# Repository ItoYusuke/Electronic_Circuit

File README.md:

Electronic_Circuit
==================

###Rubbish Devices Warehouse
##我楽多 デバイス 倉庫

Temporary list
 * I-Robot                : Motor driver and Sensor for robot.
 * LED_Blink              : Meaning as it is
 * LogicIC_CPU            : 74HCxx 4bit CPU
 * Optical_Communication  : LED or Laser light Optical communication
 * Voice_Synthesis-USB    : Voice synthesis LSI to PIC18F2550?
 * Libraries              : make devices for Eagle Libries

運用テストとして，過去の作品とかも含んでます．  
「体裁が保てていない」「処女作」「思いつき」の電子回路が多いです．  
そのうち突かれるか正式運用すると綺麗にします．  

--Implementation TEST--  
 * Eagle CAD + GitHub

A past work etc. are contained.  
"The appearance cannot be kept up. " "First work" "Straight Idea" etc...  
There are such a lot of electric circuits.   
Both are dirty.  
…It corrects it sooner or later.  

and... 

Please pay attention.   
Fool that I am!

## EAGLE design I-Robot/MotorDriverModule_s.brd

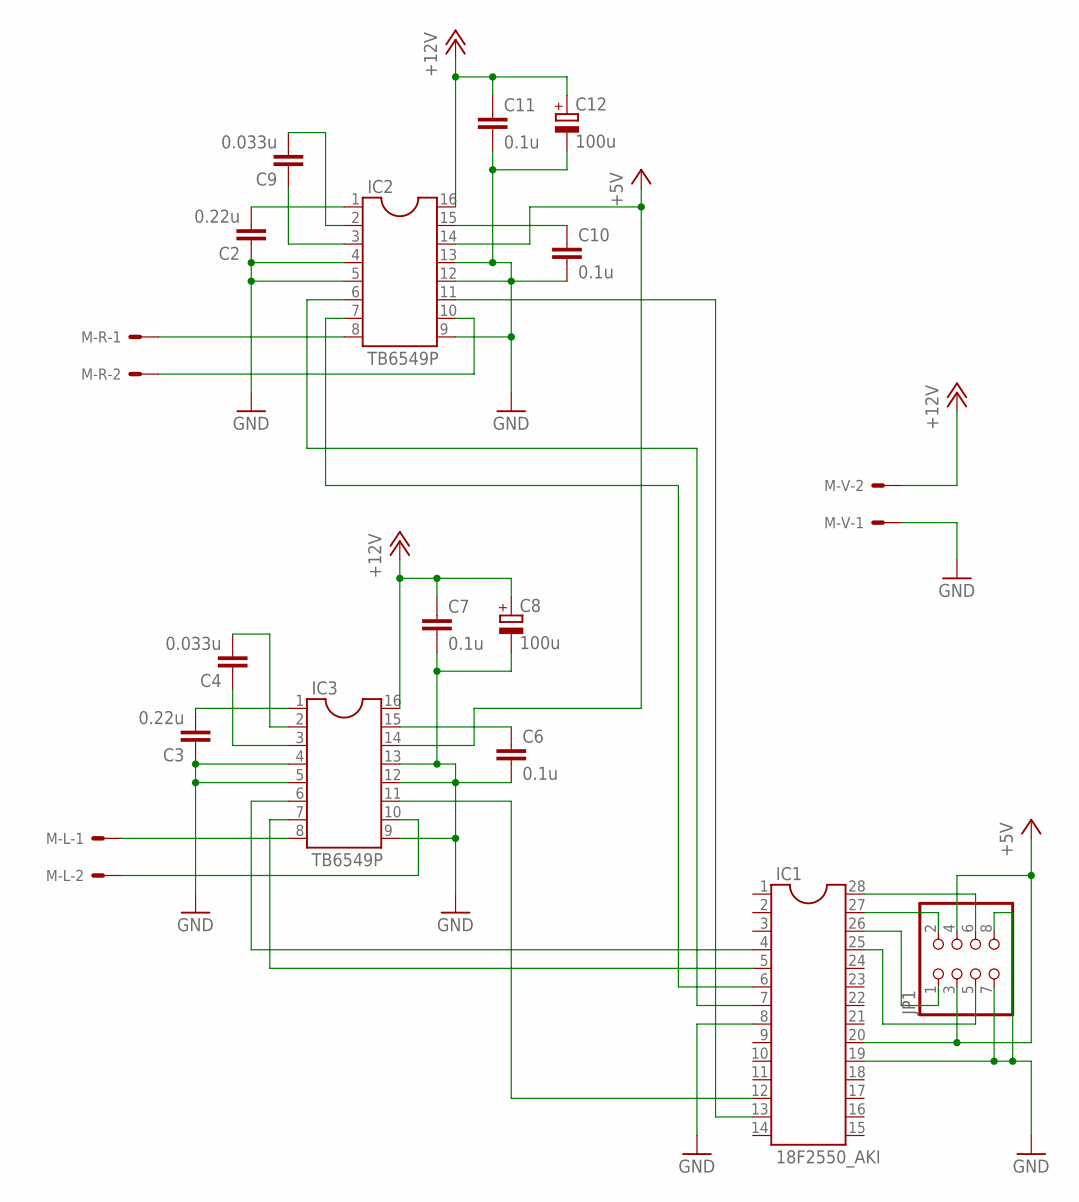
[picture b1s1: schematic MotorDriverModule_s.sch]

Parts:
C2, C3: 0.22u; C2012
C4, C9: 0.033u; C2012
C6, C7, C10, C11: 0.1u; C2012
C8, C12: 100u; D/7343-31W
IC1: 18F2550_AKI
IC2, IC3: TB6549P
JP1: PINHD-2X4; 2X04
M-L: KK-156-2
M-R: KK-156-2
M-V: KK-156-2

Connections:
+5V: IC1.20, IC2.14, IC3.14, JP1.3, JP1.4
+12V: C7.1, C8.+, C11.1, C12.+, IC2.16, IC3.16, M-V.2
GND: C2.1, C3.1, C6.2, C7.2, C8.-, C10.2, C11.2, C12.-, IC1.8, IC1.19, IC2.4, IC2.5, IC2.9, IC2.12, IC2.13, IC3.4, IC3.5, IC3.9, IC3.12, IC3.13, JP1.7, JP1.8, M-V.1
unnamed: IC1.12, IC3.11
unnamed: IC1.4, IC3.6
unnamed: IC1.5, IC3.7
unnamed: IC3.8, M-L.1
unnamed: IC3.10, M-L.2
unnamed: C3.2, IC3.1
unnamed: C4.2, IC3.2
unnamed: C4.1, IC3.3
unnamed: C6.1, IC3.15
unnamed: IC1.28, JP1.6
unnamed: IC1.13, IC2.11
unnamed: IC1.7, IC2.6
unnamed: IC1.6, IC2.7
unnamed: IC2.8, M-R.1
unnamed: IC1.27, JP1.2
unnamed: IC1.26, JP1.1
unnamed: IC1.25, JP1.5
unnamed: IC2.10, M-R.2
unnamed: C2.2, IC2.1
unnamed: C9.2, IC2.2
unnamed: C9.1, IC2.3
unnamed: C10.1, IC2.15

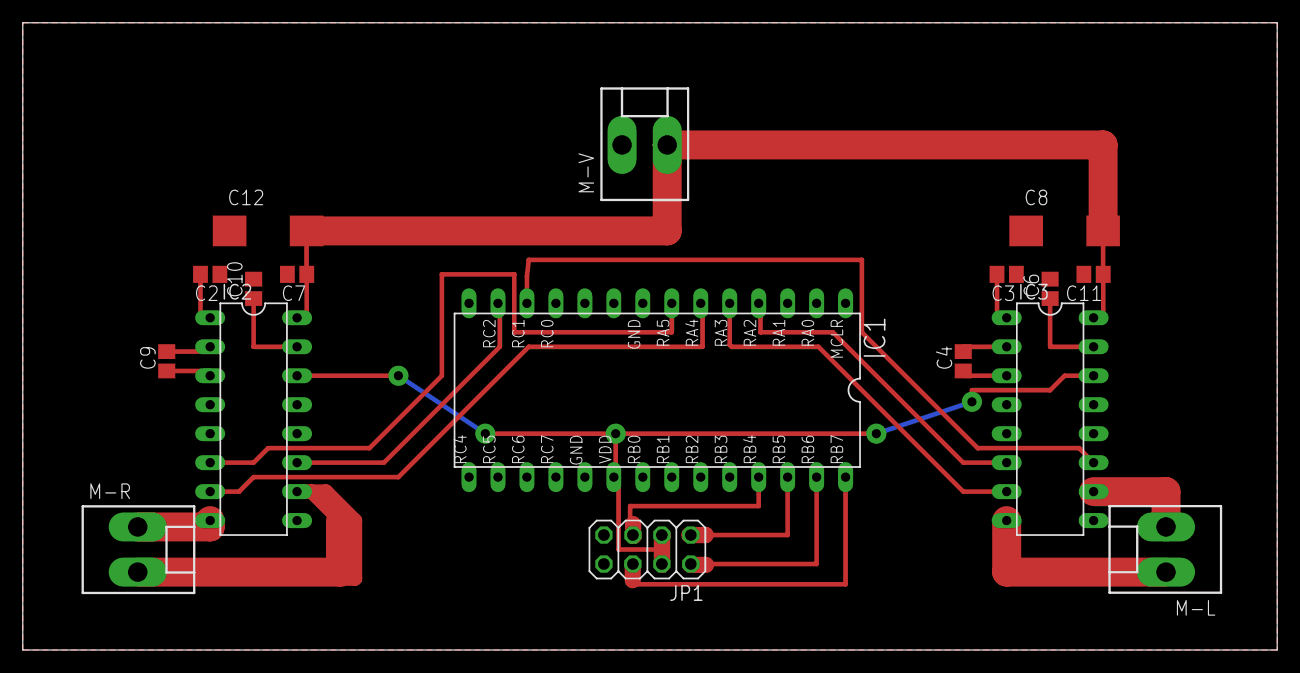
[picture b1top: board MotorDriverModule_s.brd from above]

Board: 2 copper layers, 110.0 x 55.0 mm, 17 parts (0 on the bottom side), 25 nets.

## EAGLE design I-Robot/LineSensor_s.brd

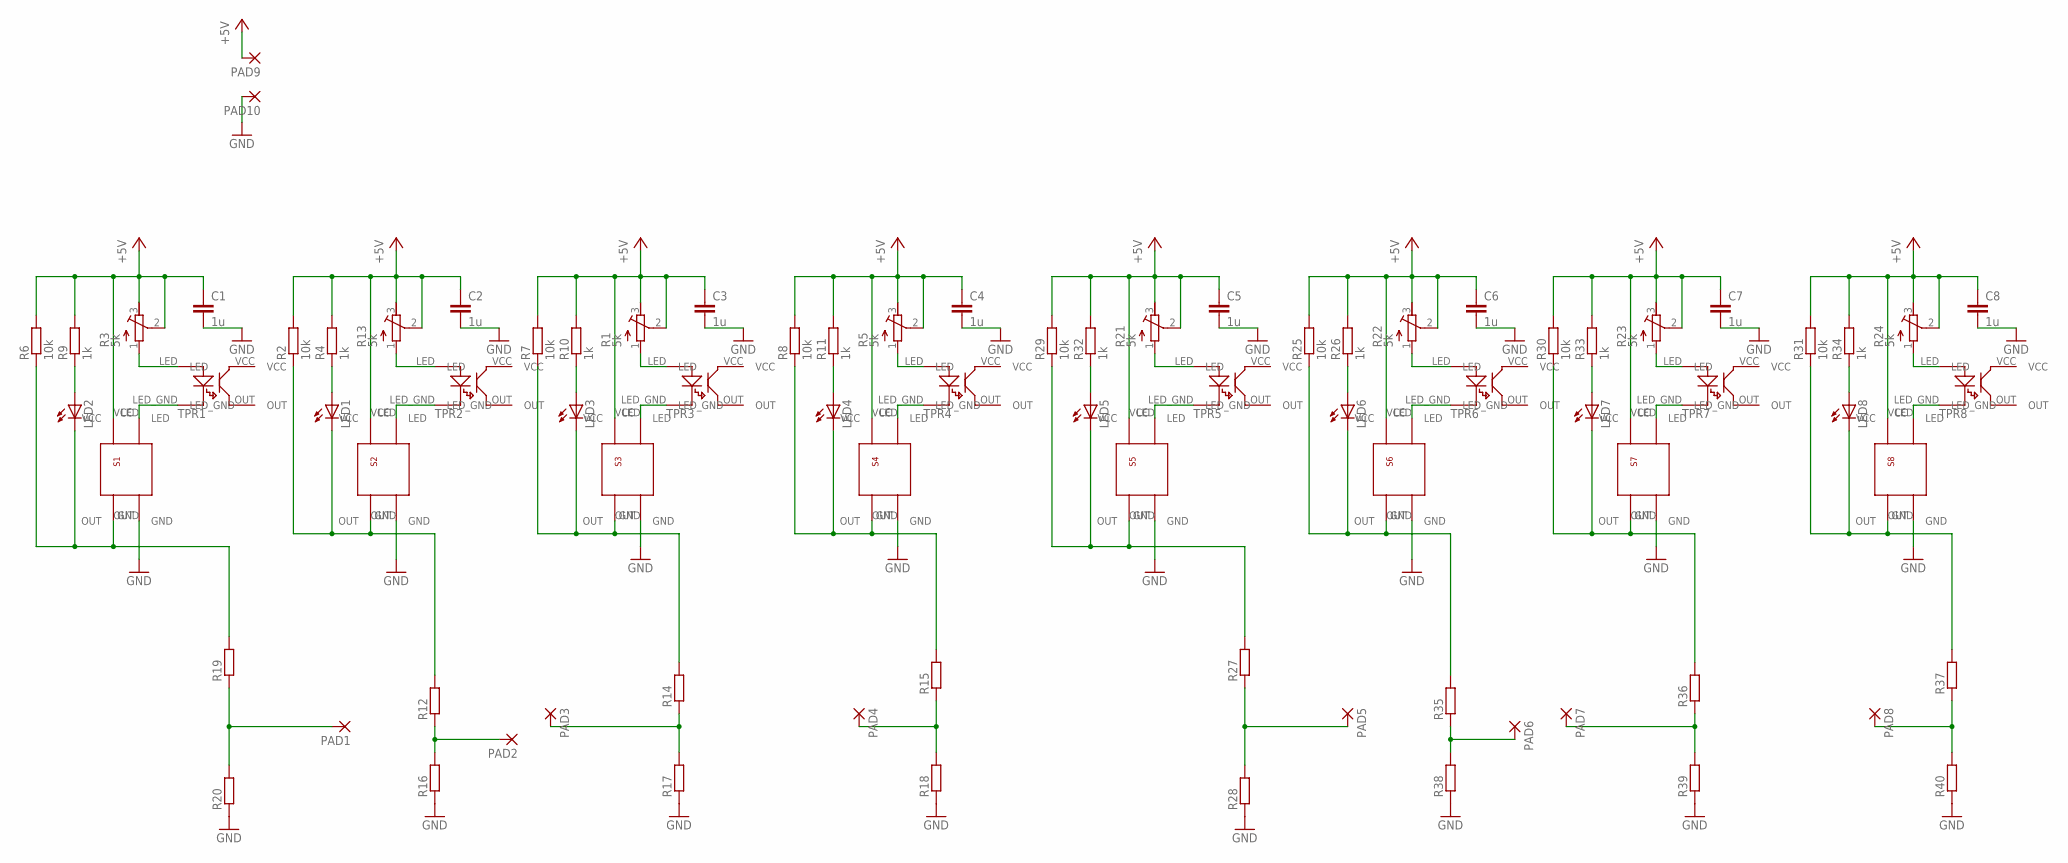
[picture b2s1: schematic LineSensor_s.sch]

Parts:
C1, C2, C3, C4, C5, C6, C7, C8: 1u; C1005
LED1, LED2, LED3, LED4, LED5, LED6, LED7, LED8: LEDSMT1206; 1206
PAD1, PAD2, PAD3, PAD4, PAD5, PAD6, PAD7, PAD8, PAD9, PAD10: SMD5; SMD2,54-5,08
R1, R3, R5, R13, R21, R22, R23, R24: 5k; RTRIM3374
R2, R6, R7, R8, R25, R29, R30, R31: 10k; R2012
R4, R9, R10, R11, R26, R32, R33, R34: 1k; R2012
R12, R14, R15, R16, R17, R18, R19, R20, R27, R28, R35, R36, R37, R38, R39, R40: R-EU_R2012; R2012
S1, S2, S3, S4, S5, S6, S7, S8: S-IC
TPR1, TPR2, TPR3, TPR4, TPR5, TPR6, TPR7, TPR8: TPR

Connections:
+5V: C1.1, C2.1, C3.1, C4.1, C5.1, C6.1, C7.1, C8.1, PAD9.1, R1.2 (S), R1.3 (A), R2.2, R3.2 (S), R3.3 (A), R4.2, R5.2 (S), R5.3 (A), R6.2, R7.2, R8.2, R9.2, R10.2, R11.2, R13.2 (S), R13.3 (A), R21.2 (S), R21.3 (A), R22.2 (S), R22.3 (A), R23.2 (S), R23.3 (A), R24.2 (S), R24.3 (A), R25.2, R26.2, R29.2, R30.2, R31.2, R32.2, R33.2, R34.2, S1.VCC, S2.VCC, S3.VCC, S4.VCC, S5.VCC, S6.VCC, S7.VCC, S8.VCC
GND: C1.2, C2.2, C3.2, C4.2, C5.2, C6.2, C7.2, C8.2, PAD10.1, R16.1, R17.1, R18.1, R20.1, R28.1, R38.1, R39.1, R40.1, S1.GND, S2.GND, S3.GND, S4.GND, S5.GND, S6.GND, S7.GND, S8.GND
unnamed: S2.LED, TPR2.LED_GND
unnamed: R13.1 (E), TPR2.LED
unnamed: S1.LED, TPR1.LED_GND
unnamed: R3.1 (E), TPR1.LED
unnamed: LED2.C, R6.1, R19.2, S1.OUT
unnamed: LED2.A, R9.1
unnamed: LED1.C, R2.1, R12.2, S2.OUT
unnamed: LED1.A, R4.1
unnamed: S3.LED, TPR3.LED_GND
unnamed: R1.1 (E), TPR3.LED
unnamed: LED3.C, R7.1, R14.2, S3.OUT
unnamed: LED3.A, R10.1
unnamed: S4.LED, TPR4.LED_GND
unnamed: R5.1 (E), TPR4.LED
unnamed: LED4.C, R8.1, R15.2, S4.OUT
unnamed: LED4.A, R11.1
unnamed: PAD2.1, R12.1, R16.2
unnamed: PAD3.1, R14.1, R17.2
unnamed: PAD4.1, R15.1, R18.2
unnamed: S5.LED, TPR5.LED_GND
unnamed: R21.1 (E), TPR5.LED
unnamed: LED5.C, R27.2, R29.1, S5.OUT
unnamed: LED5.A, R32.1
unnamed: S6.LED, TPR6.LED_GND
unnamed: R22.1 (E), TPR6.LED
unnamed: LED6.C, R25.1, R35.2, S6.OUT
unnamed: LED6.A, R26.1
unnamed: S7.LED, TPR7.LED_GND
unnamed: R23.1 (E), TPR7.LED
unnamed: LED7.C, R30.1, R36.2, S7.OUT
unnamed: LED7.A, R33.1
unnamed: S8.LED, TPR8.LED_GND
unnamed: R24.1 (E), TPR8.LED
unnamed: LED8.C, R31.1, R37.2, S8.OUT
unnamed: LED8.A, R34.1
unnamed: PAD5.1, R27.1, R28.2
unnamed: PAD6.1, R35.1, R38.2
unnamed: PAD7.1, R36.1, R39.2
unnamed: PAD8.1, R37.1, R40.2
unnamed: PAD1.1, R19.1, R20.2
VCC: TPR1.VCC, TPR2.VCC, TPR3.VCC, TPR4.VCC, TPR5.VCC, TPR6.VCC, TPR7.VCC, TPR8.VCC

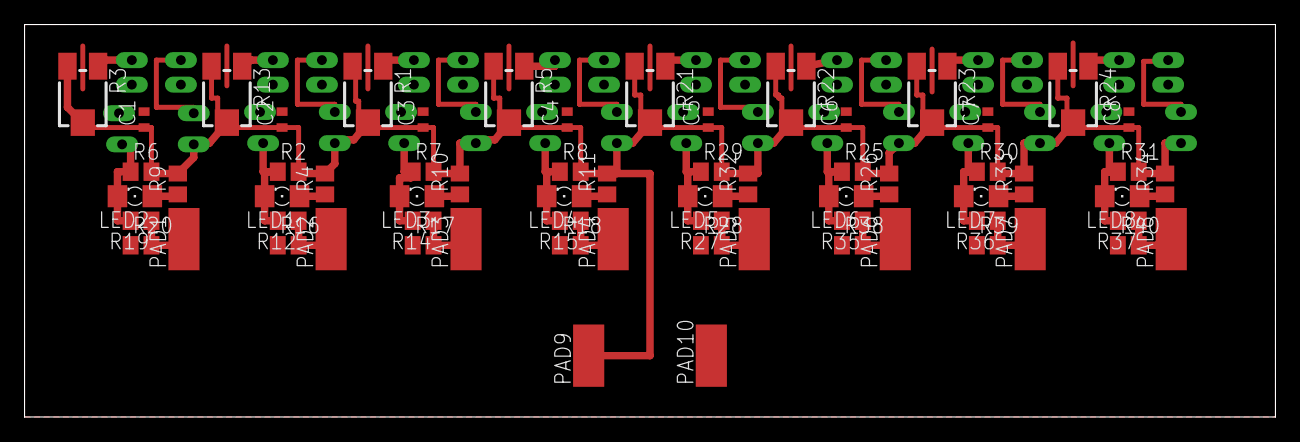
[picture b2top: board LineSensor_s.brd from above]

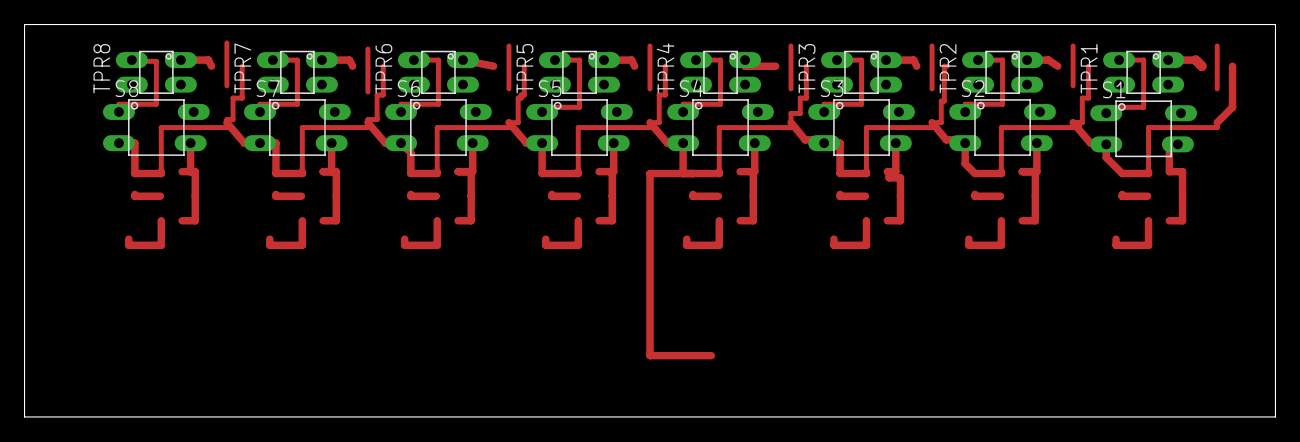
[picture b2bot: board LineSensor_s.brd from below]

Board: 2 copper layers, 102.0 x 32.0 mm, 82 parts (16 on the bottom side), 43 nets.

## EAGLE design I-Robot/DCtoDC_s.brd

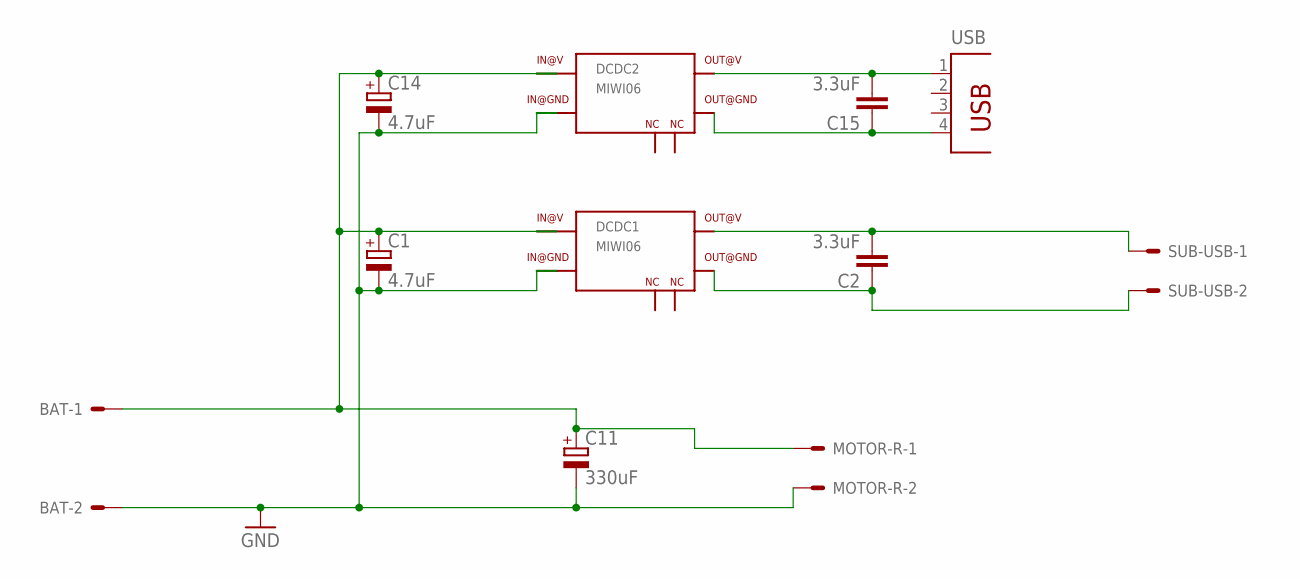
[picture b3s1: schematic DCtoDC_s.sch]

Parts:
BAT: KK-156-2
C1, C14: 4.7uF; D/7343-31W
C2, C15: 3.3uF; C3216
C11: 330uF; D/7343-31W
DCDC1, DCDC2: MIWI06
MOTOR-R: KK-156-2
SUB-USB: KK-156-2
USB: PN87520

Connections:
5V: C15.2, DCDC2.V@OUT (14), USB.1
23: DCDC1.V@IN2 (23), DCDC2.V@IN2 (23)
GND: BAT.2, C1.-, C11.-, C14.-, DCDC1.GND@IN1 (2), DCDC1.GND@IN2 (3), DCDC2.GND@IN1 (2), DCDC2.GND@IN2 (3), MOTOR-R.2
unnamed: C2.2, DCDC1.V@OUT (14), SUB-USB.1
unnamed: C2.1, DCDC1.GND@OUT (16), SUB-USB.2
unnamed: C15.1, DCDC2.GND@OUT (16), USB.4
unnamed: BAT.1, C1.+, C11.+, C14.+, DCDC1.V@IN1 (22), DCDC2.V@IN1 (22), MOTOR-R.1

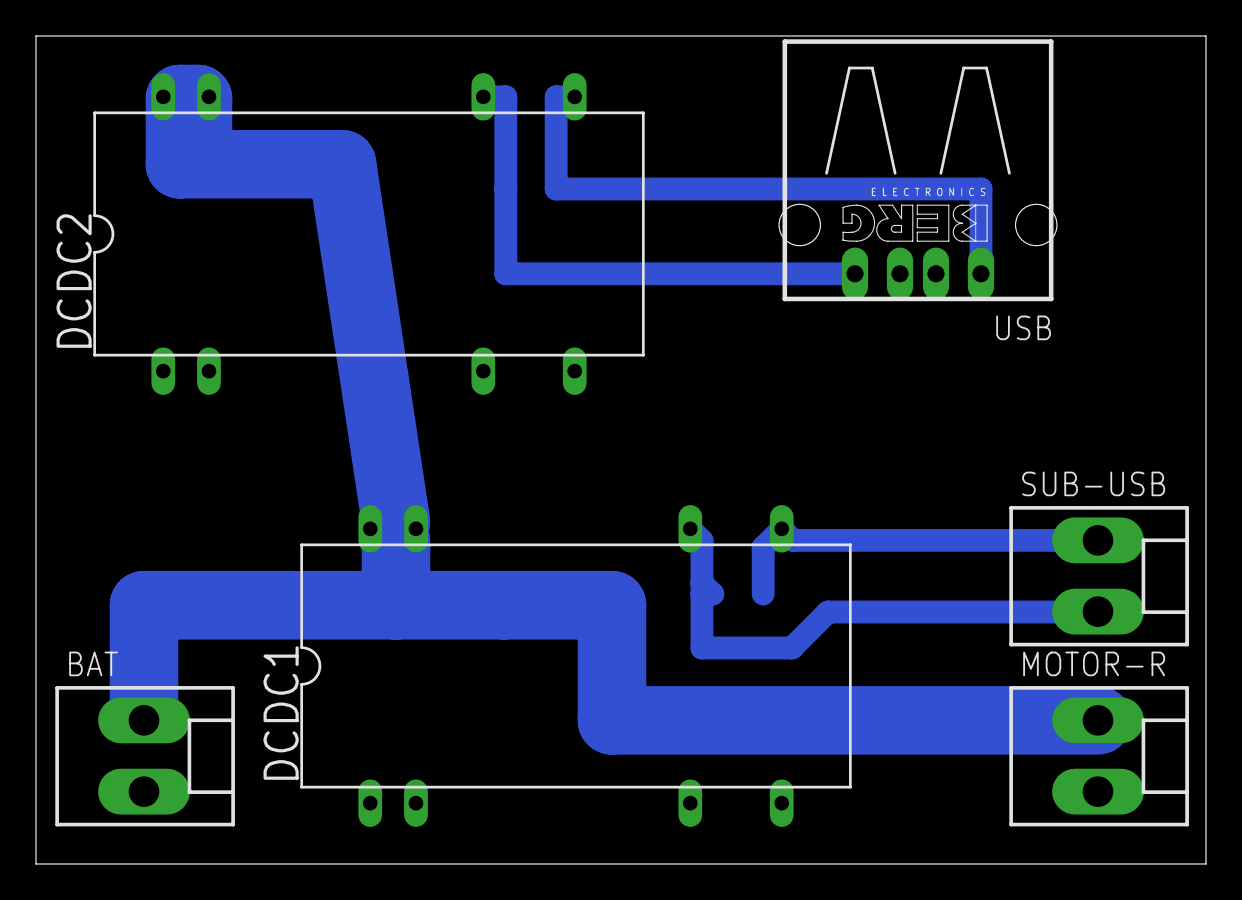
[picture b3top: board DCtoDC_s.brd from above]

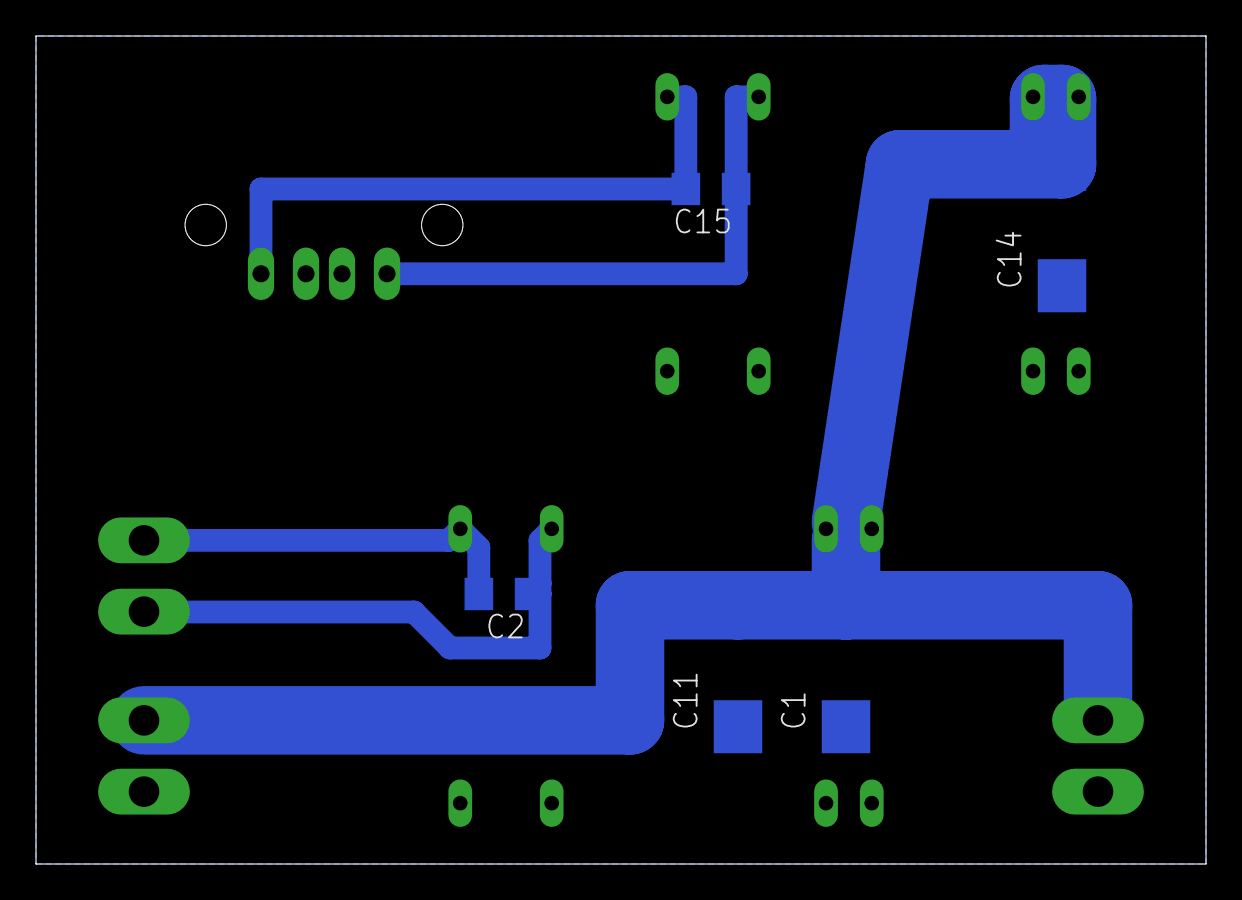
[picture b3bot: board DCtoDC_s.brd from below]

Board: 2 copper layers, 65.0 x 46.0 mm, 11 parts (5 on the bottom side), 7 nets.

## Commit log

2014-04-07 Create : LED_Blink
    EAGLE CAD 6.4
2014-04-07 updete
2014-04-07 LogicIC_CPU
    add all View
